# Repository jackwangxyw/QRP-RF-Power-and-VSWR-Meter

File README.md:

# QRP-RF-Power-and-VSWR-Meter
Compact SWR and power meter for field use

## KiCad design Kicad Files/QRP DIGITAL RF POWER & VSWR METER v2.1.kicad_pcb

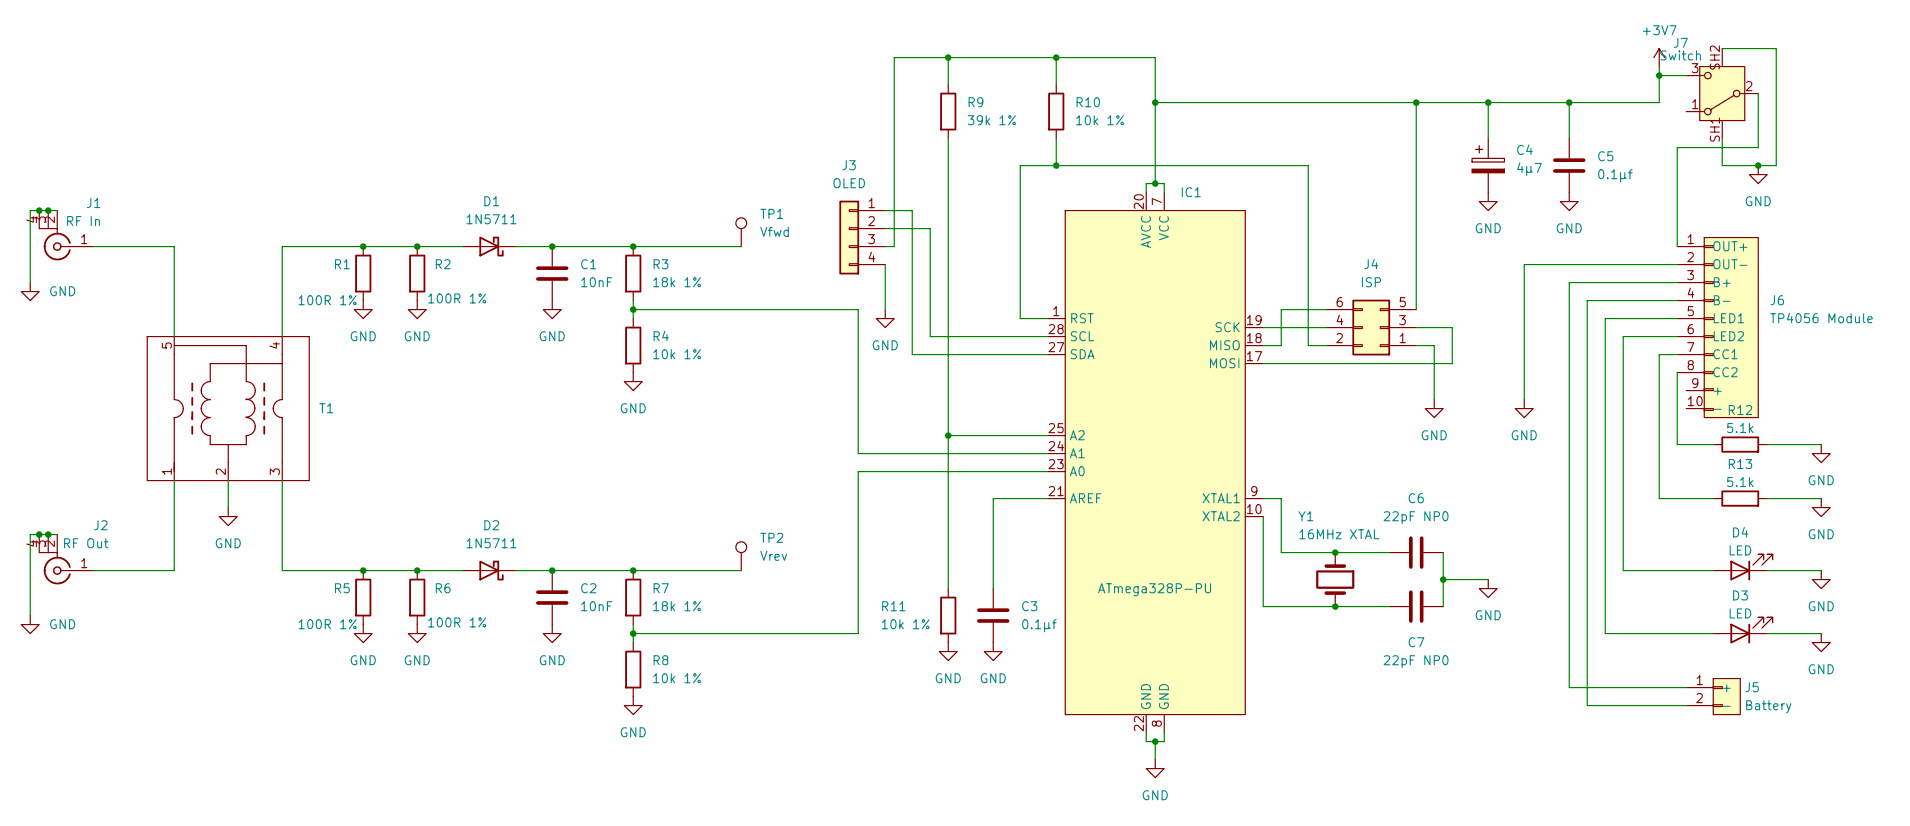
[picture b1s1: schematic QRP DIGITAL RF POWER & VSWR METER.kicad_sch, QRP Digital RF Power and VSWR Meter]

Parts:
C1, C2: 10nF; C_0805_2012Metric_Pad1.18x1.45mm_HandSolder
C3, C5: 0.1μf; C_0805_2012Metric_Pad1.18x1.45mm_HandSolder
C4: 4μ7; C_1206_3216Metric_Pad1.33x1.80mm_HandSolder
C6, C7: 22pF NP0; C_0805_2012Metric_Pad1.18x1.45mm_HandSolder
D1, D2: 1N5711; D_SOD-123
D3, D4: LED; LED_1206_3216Metric_Pad1.42x1.75mm_HandSolder
IC1: ATmega328P-PU; DIP-28_W7.62mm_LongPads
J1: RF In; Molex 0731385003
J2: RF Out; Molex 0731385003
J3: OLED; Conn_WIre_SMD_1x4
J4: ISP; PinHeader_2x03_P2.54mm_Vertical
J5: Battery; Molex_PicoBlade_53048-0210_1x02_P1.25mm_Horizontal
J6: TP4056 Module; TP4056 Type-C USB Charging Module
J7: Switch; SW_SLW-129956-4A-RA-N-D
R1, R2, R5, R6: 100R 1%; R_1206_3216Metric_Pad1.30x1.75mm_HandSolder
R3, R7: 18k 1%; R_0805_2012Metric_Pad1.20x1.40mm_HandSolder
R4, R8, R10, R11: 10k 1%; R_0805_2012Metric_Pad1.20x1.40mm_HandSolder
R9: 39k 1%; R_0805_2012Metric_Pad1.20x1.40mm_HandSolder
R12, R13: 5.1k; R_0805_2012Metric_Pad1.20x1.40mm_HandSolder
T1: Tandem Coupler 10_1
TP1: Vfwd; TestPoint_THTPad_2.5x2.5mm_Drill1.2mm
TP2: Vrev; TestPoint_THTPad_2.5x2.5mm_Drill1.2mm
Y1: 16MHz XTAL; Crystal_HC49-U_Vertical

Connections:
+3V7: C4.1, C5.1, IC1.7 (VCC), IC1.20 (AVCC), J3.3, J4.5, J7.3 (C), R9.1, R10.1
GND: C1.2, C2.2, C3.2, C4.2, C5.2, C6.1, C7.1, D3.1 (K), D4.1 (K), IC1.8 (GND), IC1.22 (GND), J1.2 (Ext), J1.3 (Ext), J1.4 (Ext), J2.2 (Ext), J2.3 (Ext), J2.4 (Ext), J3.4, J4.1, J6.2 (OUT-), J7.SH1, J7.SH2, R1.2, R2.2, R4.2, R5.2, R6.2, R8.2, R11.2, R12.2, R13.2, T1.2
unnamed: D1.2 (A), R1.1, R2.1, T1.4
unnamed: C1.1, D1.1 (K), R3.1, TP1.1 (1_1)
unnamed: D2.2 (A), R5.1, R6.1, T1.3
unnamed: C2.1, D2.1 (K), R7.1, TP2.1 (1_1)
unnamed: D3.2 (A), J6.5 (LED1)
unnamed: D4.2 (A), J6.6 (LED2)
unnamed: IC1.23 (A0), R7.2, R8.1
unnamed: IC1.24 (A1), R3.2, R4.1
unnamed: IC1.25 (A2), R9.2, R11.1
unnamed: C3.1, IC1.21 (AREF)
unnamed: IC1.18 (MISO), J4.6
unnamed: IC1.17 (MOSI), J4.3
unnamed: IC1.1 (RST), J4.2, R10.2
unnamed: IC1.19 (SCK), J4.4
unnamed: IC1.28 (SCL), J3.2
unnamed: IC1.27 (SDA), J3.1
unnamed: C6.2, IC1.9 (XTAL1), Y1.1
unnamed: C7.2, IC1.10 (XTAL2), Y1.2
unnamed: J1.1 (In), T1.5
unnamed: J2.1 (In), T1.1
unnamed: J5.1 (+), J6.3 (B+)
unnamed: J5.2 (-), J6.4 (B-)
unnamed: J6.7 (CC1), R13.1
unnamed: J6.8 (CC2), R12.1
unnamed: J6.1 (OUT+), J7.2 (B)

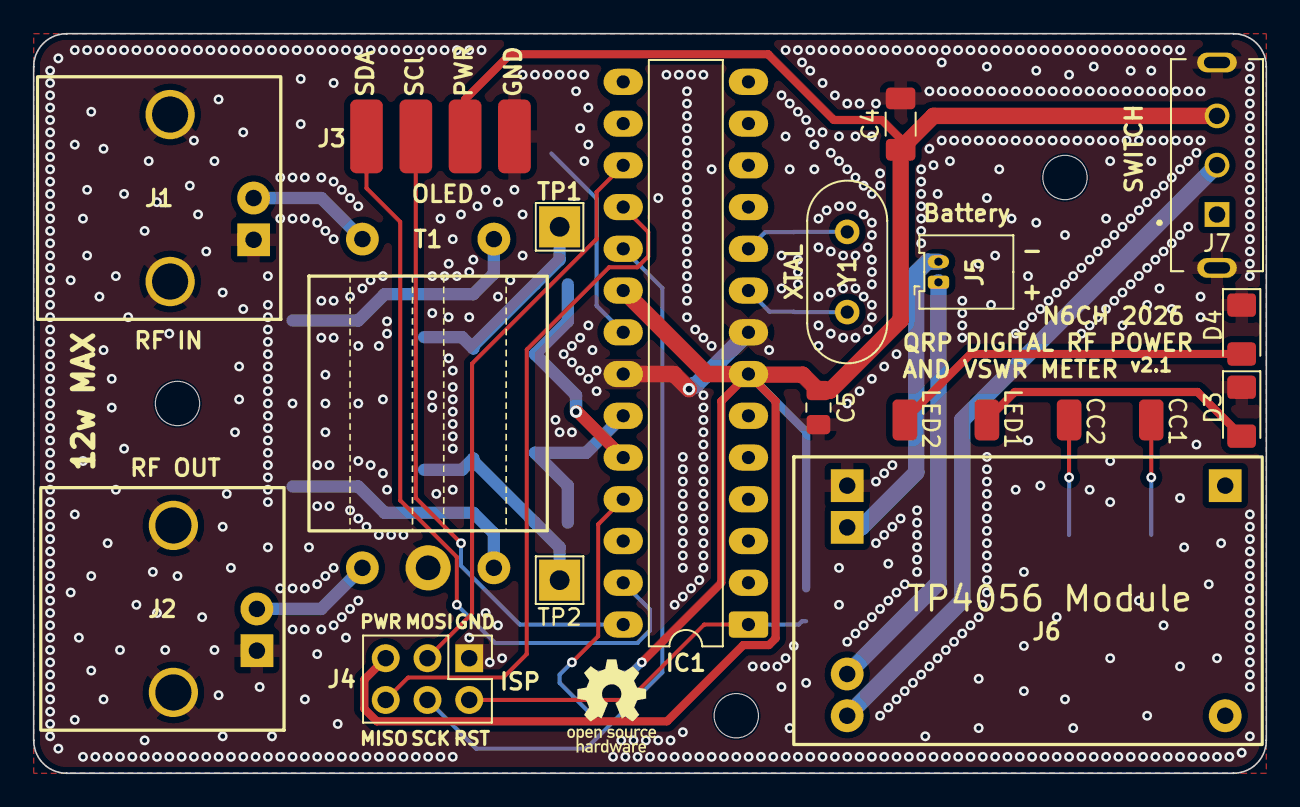
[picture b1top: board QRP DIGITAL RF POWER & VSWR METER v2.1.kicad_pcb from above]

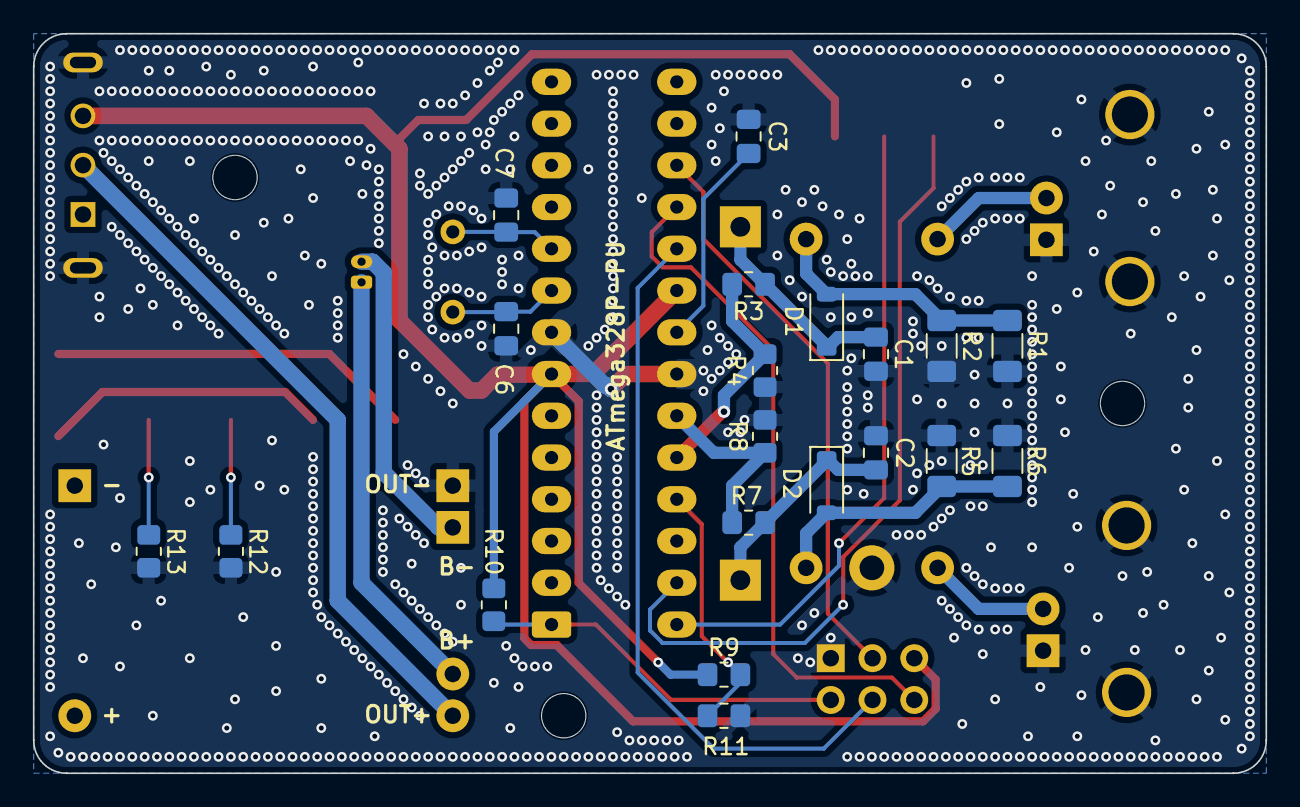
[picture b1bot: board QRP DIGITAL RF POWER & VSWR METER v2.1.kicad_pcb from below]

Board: 2 copper layers, 75.0 x 45.0 mm, 36 parts (20 on the bottom side), 27 nets.

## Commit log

2026-03-26 Add Gerber Files
2026-03-26 Add Kicad Files
2026-03-26 Rename QRP DIGITAL RF POWER AND VSWR METER Gerbers.zip to Gerbers/QRP DIGITAL RF POWER AND VSWR METER Gerbers.zip
2026-03-26 Rename RF Power and VSWR Meter Connector Panel Gerbers.zip to Gerbers/RF Power and VSWR Meter Connector Panel Gerbers.zip
2026-03-26 Rename QRP DIGITAL RF POWER & VSWR METER.kicad_pcb to Kicad Files/QRP DIGITAL RF POWER & VSWR METER.kicad_pcb
2026-03-26 Rename QRP DIGITAL RF POWER & VSWR METER.kicad_pro to Kicad Files/QRP DIGITAL RF POWER & VSWR METER.kicad_pro
2026-03-26 Rename QRP DIGITAL RF POWER & VSWR METER.kicad_sch to Kicad Files/QRP DIGITAL RF POWER & VSWR METER.kicad_sch
2026-03-26 Rename RF Power and VSWR Meter Connector Panel.kicad_pcb to Kicad Files/RF Power and VSWR Meter Connector Panel.kicad_pcb
2026-03-26 Rename RF Power and VSWR Meter Connector Panel.kicad_pro to Kicad Files/RF Power and VSWR Meter Connector Panel.kicad_pro
2026-03-26 Rename RF Power and VSWR Meter Connector Panel Gerbers.zip to RF Power and VSWR Meter Connector Panel Gerbers v1.0.zip
2026-03-26 Rename QRP DIGITAL RF POWER AND VSWR METER Gerbers.zip to QRP DIGITAL RF POWER AND VSWR METER Gerbers v2.1.zip
2026-03-26 Rename QRP DIGITAL RF POWER & VSWR METER.kicad_pcb to QRP DIGITAL RF POWER & VSWR METER v2.1.kicad_pcb
2026-03-26 Rename QRP DIGITAL RF POWER & VSWR METER.kicad_pro to QRP DIGITAL RF POWER & VSWR METER v2.1.kicad_pro
2026-03-26 Rename QRP DIGITAL RF POWER & VSWR METER.kicad_sch to QRP DIGITAL RF POWER & VSWR METER v2.1.kicad_sch
2026-03-26 Rename RF Power and VSWR Meter Connector Panel.kicad_pcb to RF Power and VSWR Meter Connector Panel v1.0.kicad_pcb
2026-03-26 Rename RF Power and VSWR Meter Connector Panel.kicad_pro to RF Power and VSWR Meter Connector Panel v1.0.kicad_pro
2026-03-26 Create LICENSE
